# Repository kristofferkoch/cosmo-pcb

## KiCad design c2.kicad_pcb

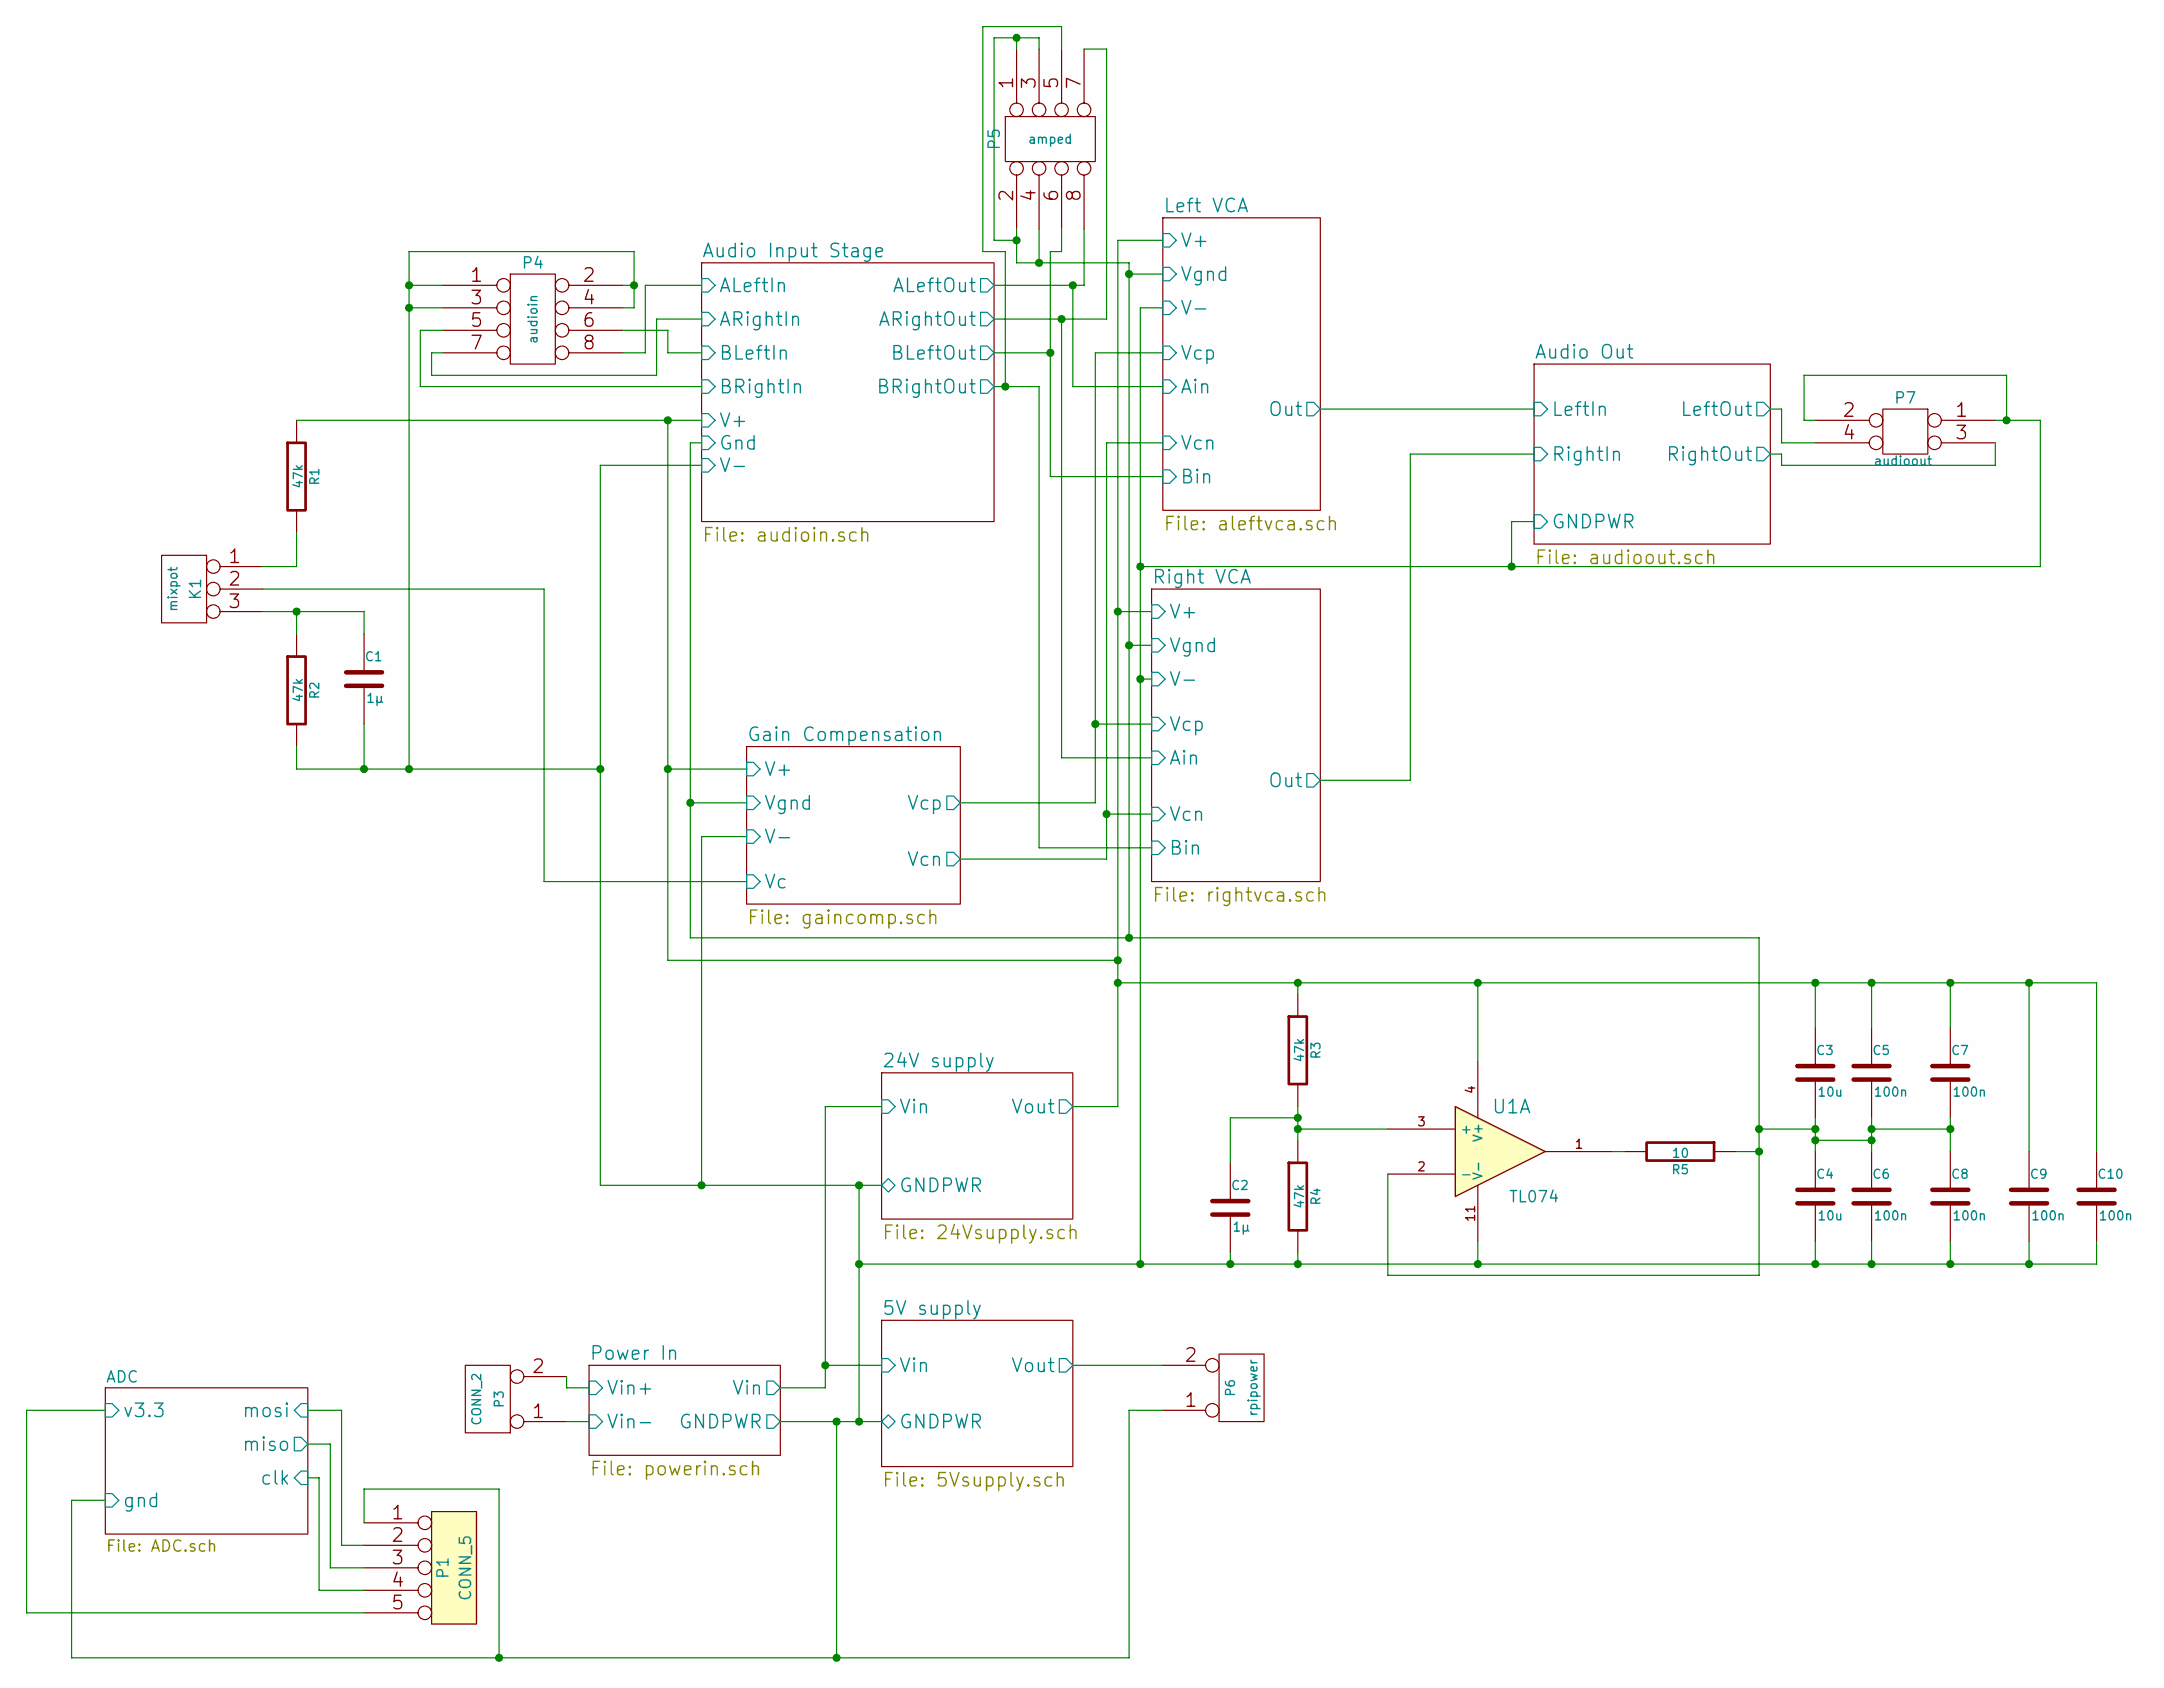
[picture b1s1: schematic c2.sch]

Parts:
C1, C2: 1µ
C3, C4: 10u
C5, C6, C7, C8, C9, C10: 100n
K1: mixpot
P1: CONN_5
P3: CONN_2
P4: audioin
P5: amped
P6: rpipower
P7: audioout
R1, R2, R3, R4: 47k
R5: 10
U1: TL074

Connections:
/5V supply/Vout: P6.2 (PM); also elsewhere on the board
/ADC/clk: P1.4; also elsewhere on the board
/ADC/miso: P1.3; also elsewhere on the board
/ADC/mosi: P1.2; also elsewhere on the board
/ADC/v3.3: P1.5; also elsewhere on the board
/Audio Input Stage/ALeftIn: P4.8; also elsewhere on the board
/Audio Input Stage/ALeftOut: P5.8; also elsewhere on the board
/Audio Input Stage/ARightIn: P4.7; also elsewhere on the board
/Audio Input Stage/ARightOut: P5.7; also elsewhere on the board
/Audio Input Stage/BLeftIn: P4.6; also elsewhere on the board
/Audio Input Stage/BLeftOut: P5.6; also elsewhere on the board
/Audio Input Stage/BRightIn: P4.5; also elsewhere on the board
/Audio Input Stage/BRightOut: P5.5; also elsewhere on the board
/Audio Input Stage/Gnd: C3.2, C4.1, C5.2, C6.1, C7.2, C8.1, P5.1, P5.2, P5.3, P5.4, R5.1, U1.2 (-); also elsewhere on the board
/Audio Input Stage/V+: C3.1, C5.1, C7.1, C9.1, C10.1, R1.1, R3.1, U1.4 (V+); also elsewhere on the board
/Audio Out/LeftOut: P7.4; also elsewhere on the board
/Audio Out/RightOut: P7.3; also elsewhere on the board
/Gain Compensation/Vc: K1.2 (PM); also elsewhere on the board
/Power In/Vin+: P3.2 (PM); also elsewhere on the board
GNDPWR: C1.2, C2.2, C4.2, C6.2, C8.2, C9.2, C10.2, P1.1, P3.1, P4.1, P4.2, P4.3, P4.4, P6.1, P7.1, P7.2, R2.2, R4.2, U1.11 (V-); also elsewhere on the board
unnamed: C1.1, K1.3, R2.1
unnamed: C2.1, R3.2, R4.1, U1.3 (+)
unnamed: K1.1, R1.2
unnamed: R5.2, U1.1

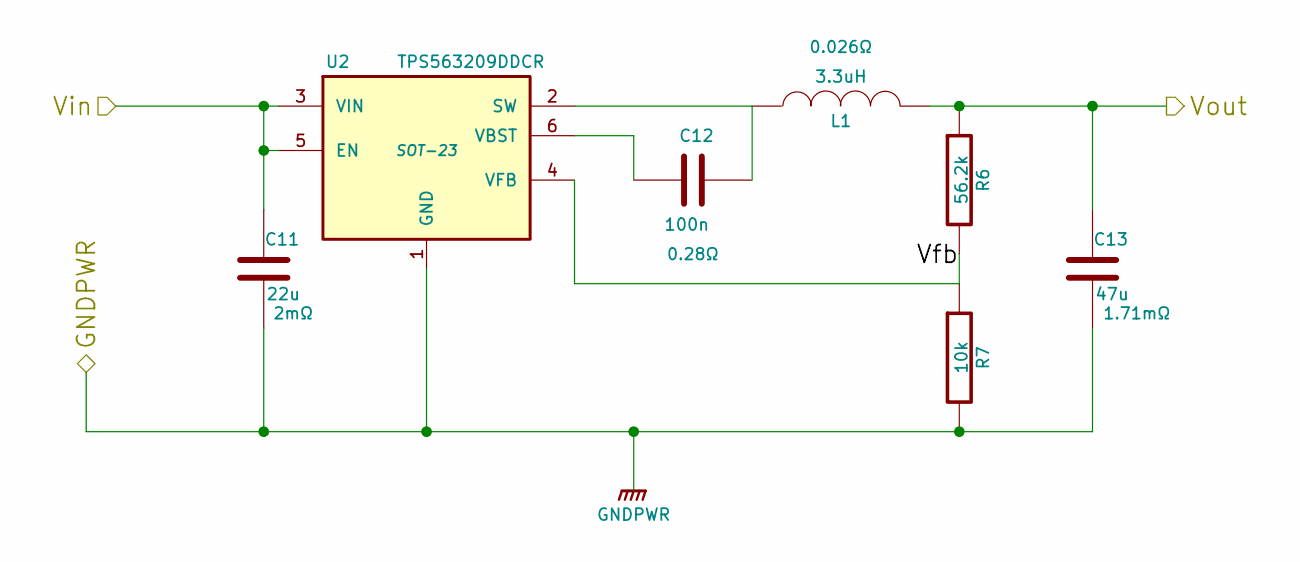
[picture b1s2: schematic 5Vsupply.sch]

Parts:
C11: 22u
C12: 100n
C13: 47u
L1: 3.3uH; Part XAL4030-332MEB
R6: 56.2k
R7: 10k
U2: TPS563209DDCR; SOT-23

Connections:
/5V supply/Vfb: R6.2, R7.1, U2.4 (VFB)
/5V supply/Vout: C13.1, L1.2, R6.1; also elsewhere on the board
/24V supply/Vin: C11.1, U2.3 (VIN), U2.5 (EN); also elsewhere on the board
GNDPWR: C11.2, C13.2, R7.2, U2.1 (GND); also elsewhere on the board
unnamed: C12.1, L1.1, U2.2 (SW)
unnamed: C12.2, U2.6 (VBST)

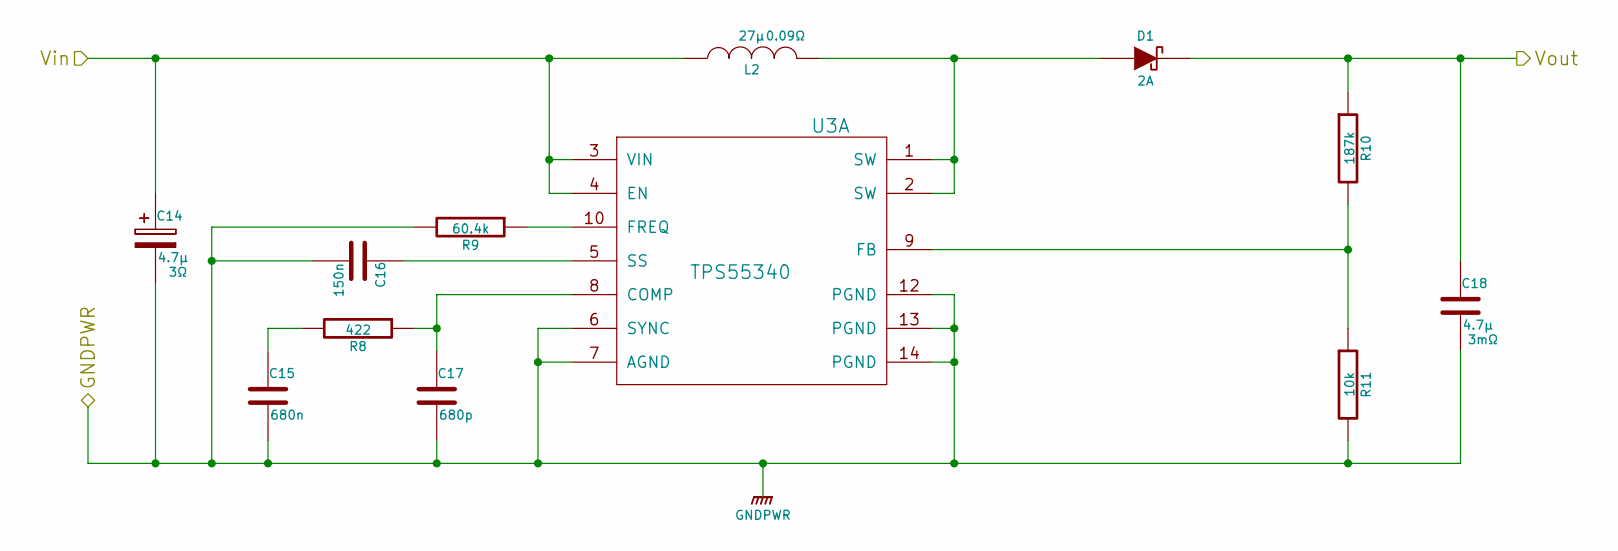
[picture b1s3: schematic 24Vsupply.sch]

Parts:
C14, C18: 4.7µ
C15: 680n
C16: 150n
C17: 680p
D1: 2A
L2: 27µ; Part DR0608-273L
R8: 422
R9: 60.4k
R10: 187k; Tolerance 1%
R11: 10k
U3: TPS55340

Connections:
/24V supply/Vin: C14.1, L2.1, U3.3 (VIN), U3.4 (EN); also elsewhere on the board
/Audio Input Stage/V+: C18.1, D1.2 (K), R10.1; also elsewhere on the board
GNDPWR: C14.2, C15.2, C16.2, C17.2, C18.2, R9.2, R11.2, U3.6 (SYNC), U3.7 (AGND), U3.12 (PGND), U3.13 (PGND), U3.14 (PGND); also elsewhere on the board
unnamed: C15.1, R8.2
unnamed: C16.1, U3.5 (SS)
unnamed: C17.1, R8.1, U3.8 (COMP)
unnamed: D1.1 (A), L2.2, U3.1 (SW), U3.2 (SW)
unnamed: R9.1, U3.10 (FREQ)
unnamed: R10.2, R11.1, U3.9 (FB)

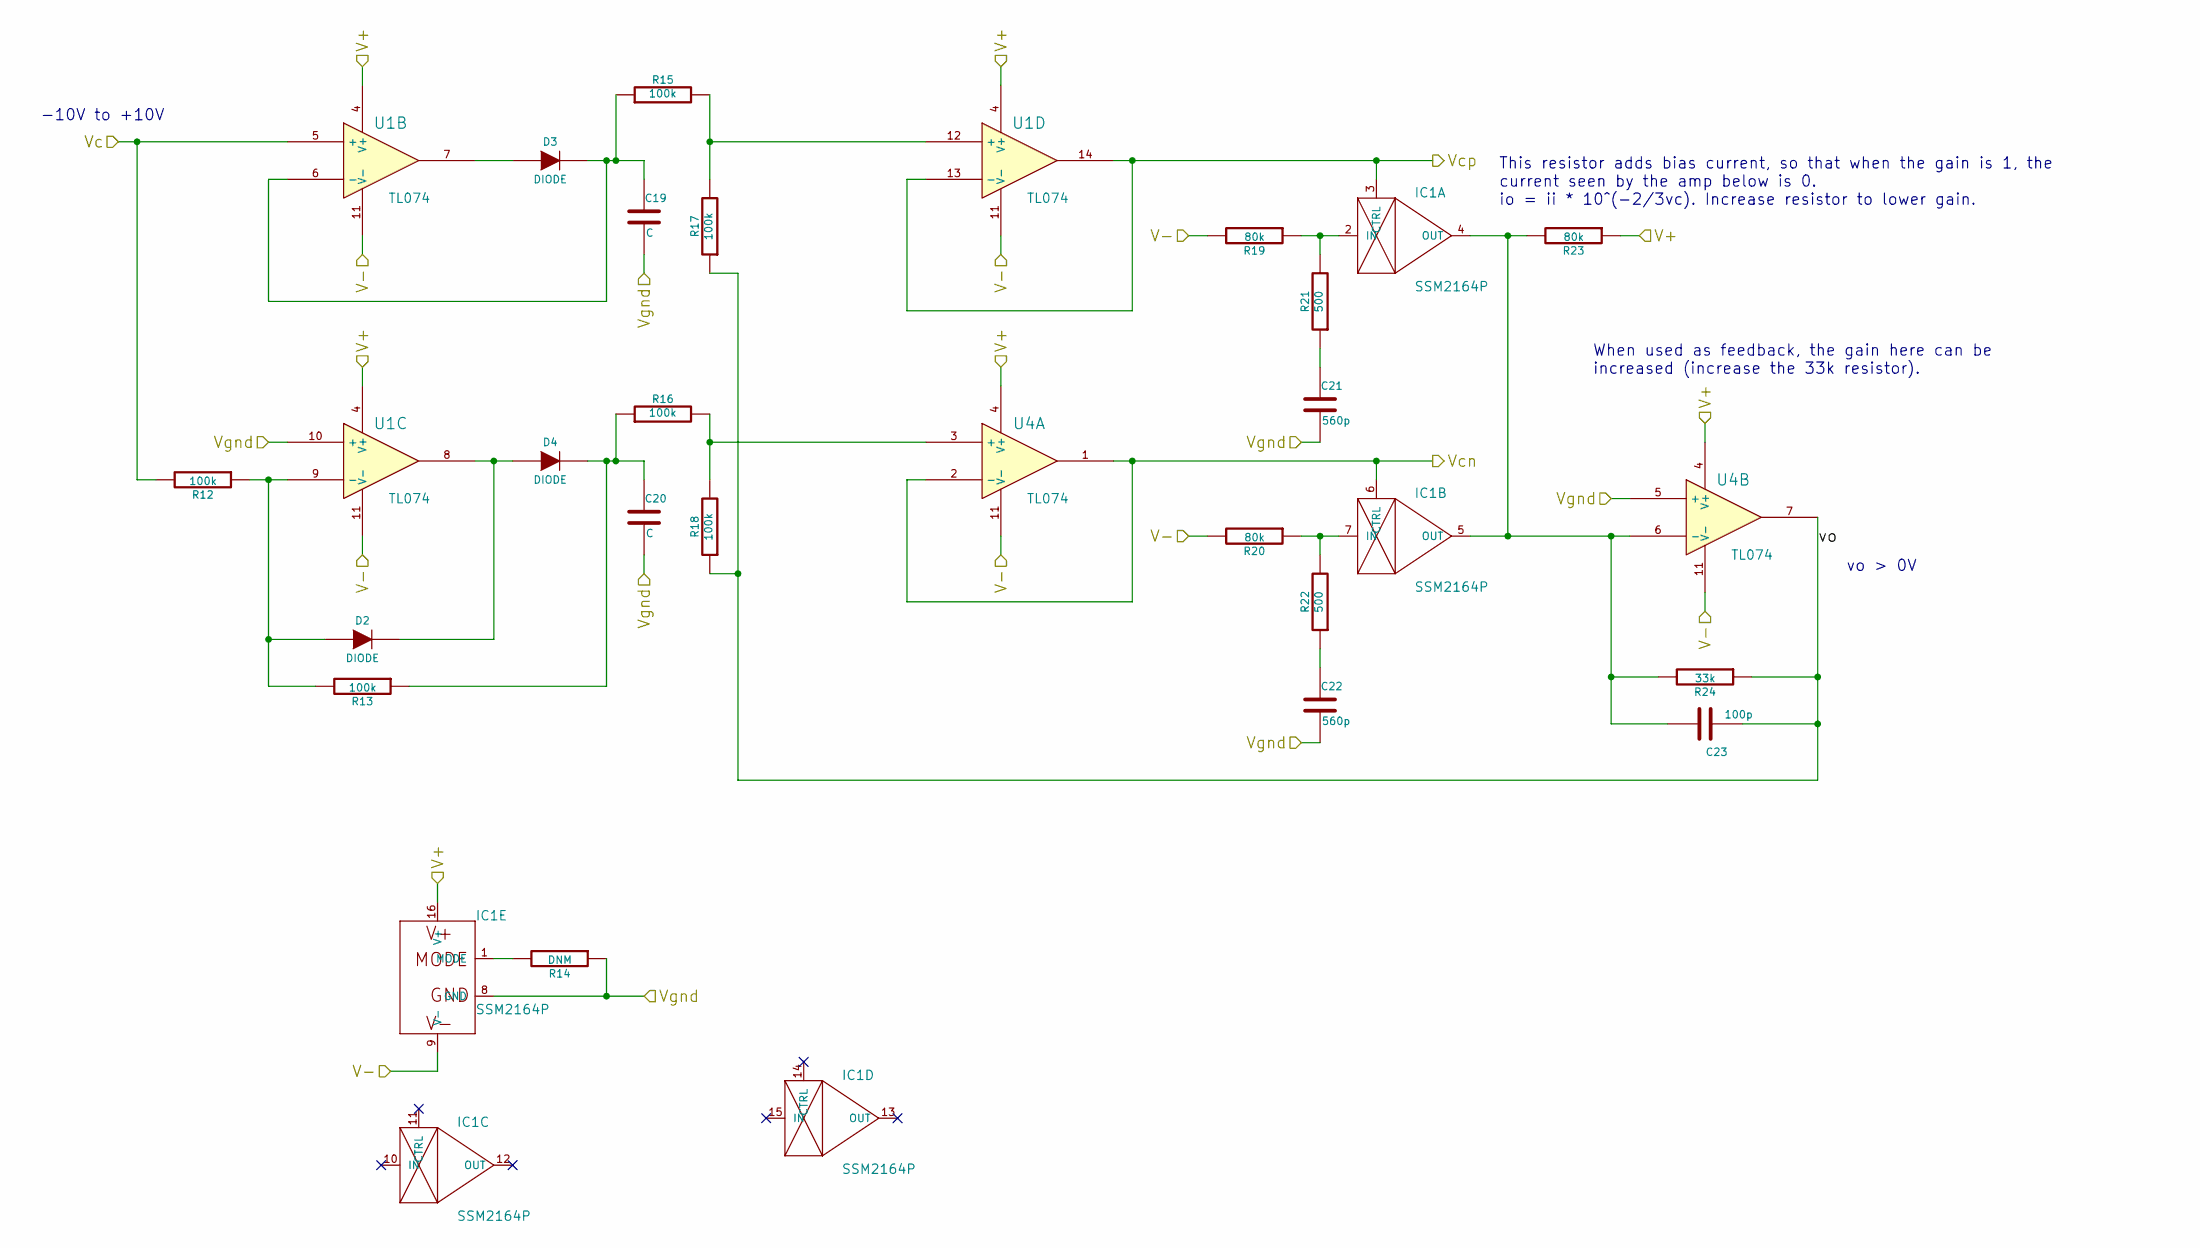
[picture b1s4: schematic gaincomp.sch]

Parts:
C19, C20: C
C21, C22: 560p
C23: 100p
D2, D3, D4: DIODE
IC1: SSM2164P; ssm2164-DIL16
R12, R13, R15, R16, R17, R18: 100k
R14: DNM
R19, R20, R23: 80k
R21, R22: 500
R24: 33k
U1, U4: TL074

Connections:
/Audio Input Stage/Gnd: C19.2, C20.2, C21.2, C22.2, IC1.8 (GND), R14.1, U1.10 (+), U4.5 (+); also elsewhere on the board
/Audio Input Stage/V+: IC1.16 (V+), R23.1, U1.4 (V+), U4.4 (V+); also elsewhere on the board
/Gain Compensation/Vc: R12.2, U1.5 (+); also elsewhere on the board
/Gain Compensation/Vcn: IC1.6 (CTRL), U4.1, U4.2 (-); also elsewhere on the board
/Gain Compensation/Vcp: IC1.3 (CTRL), U1.13 (-), U1.14; also elsewhere on the board
/Gain Compensation/vo: C23.1, R17.1, R18.1, R24.1, U4.7
GNDPWR: IC1.9 (V-), R19.2, R20.2, U1.11 (V-), U4.11 (V-); also elsewhere on the board
unnamed: C19.1, D3.2 (K), R15.1, U1.6 (-)
unnamed: C20.1, D4.2 (K), R13.1, R16.1
unnamed: C21.1, R21.1
unnamed: C22.1, R22.1
unnamed: C23.2, IC1.4 (OUT), IC1.5 (OUT), R23.2, R24.2, U4.6 (-)
unnamed: D2.1 (A), R12.1, R13.2, U1.9 (-)
unnamed: D2.2 (K), D4.1 (A), U1.8
unnamed: D3.1 (A), U1.7
unnamed: IC1.1 (MODE), R14.2
unnamed: IC1.2 (IN), R19.1, R21.2
unnamed: IC1.7 (IN), R20.1, R22.2
unnamed: R15.2, R17.2, U1.12 (+)
unnamed: R16.2, R18.2, U4.3 (+)

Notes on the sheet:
vo > 0V
When used as feedback, the gain here can be increased (increase the 33k resistor).
This resistor adds bias current, so that when the gain is 1, the current seen by the amp below is 0. io = ii * 10^(-2/3vc). Increase resistor to lower gain.
-10V to +10V

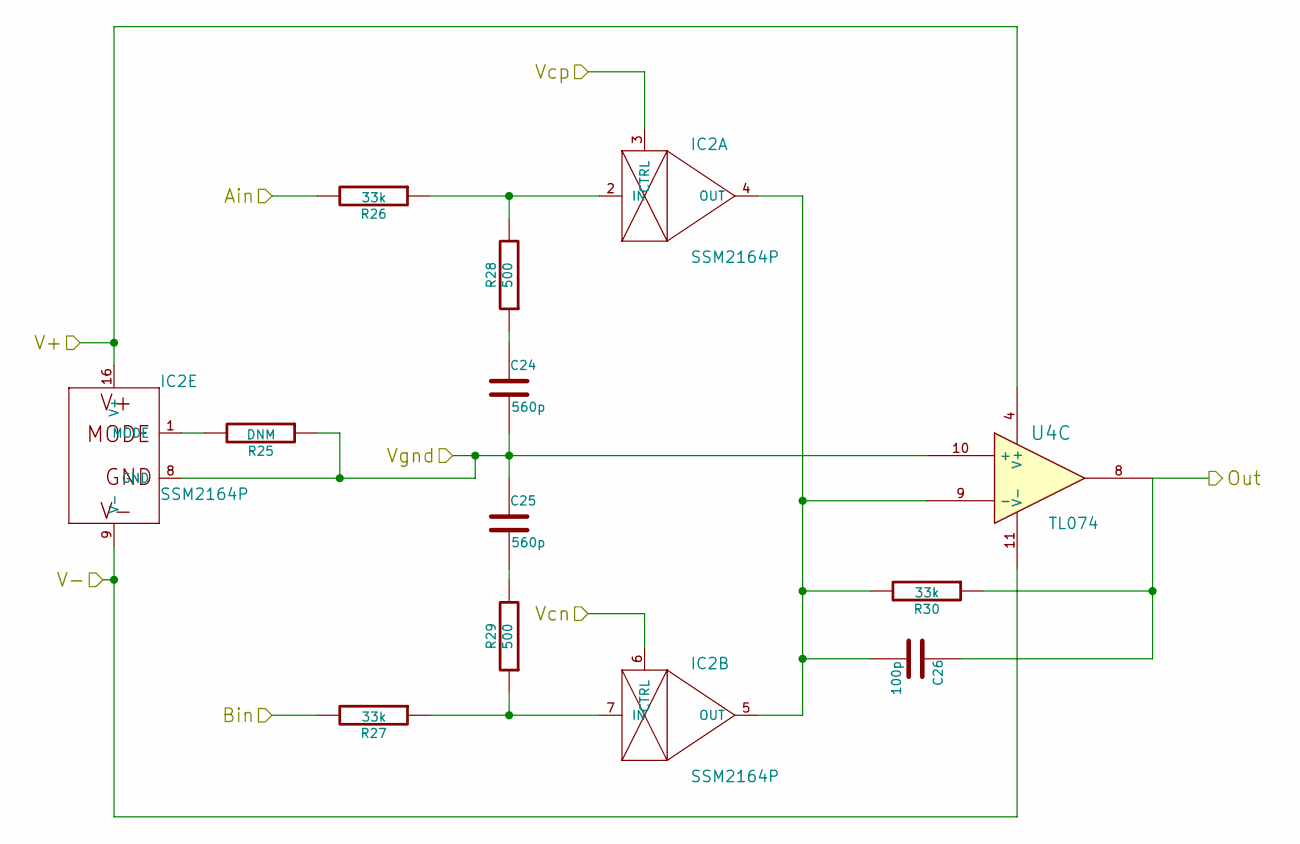
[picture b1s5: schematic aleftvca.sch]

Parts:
C24, C25: 560p
C26: 100p
IC2: SSM2164P; ssm2164-DIL16
R25: DNM
R26, R27, R30: 33k
R28, R29: 500
U4: TL074

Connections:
/Audio Input Stage/ALeftOut: R26.2; also elsewhere on the board
/Audio Input Stage/BLeftOut: R27.2; also elsewhere on the board
/Audio Input Stage/Gnd: C24.2, C25.1, IC2.8 (GND), R25.1, U4.10 (+); also elsewhere on the board
/Audio Input Stage/V+: IC2.16 (V+), U4.4 (V+); also elsewhere on the board
/Audio Out/LeftIn: C26.1, R30.1, U4.8; also elsewhere on the board
/Gain Compensation/Vcn: IC2.6 (CTRL); also elsewhere on the board
/Gain Compensation/Vcp: IC2.3 (CTRL); also elsewhere on the board
GNDPWR: IC2.9 (V-), U4.11 (V-); also elsewhere on the board
unnamed: C24.1, R28.1
unnamed: C25.2, R29.2
unnamed: C26.2, IC2.4 (OUT), IC2.5 (OUT), R30.2, U4.9 (-)
unnamed: IC2.1 (MODE), R25.2
unnamed: IC2.2 (IN), R26.1, R28.2
unnamed: IC2.7 (IN), R27.1, R29.1

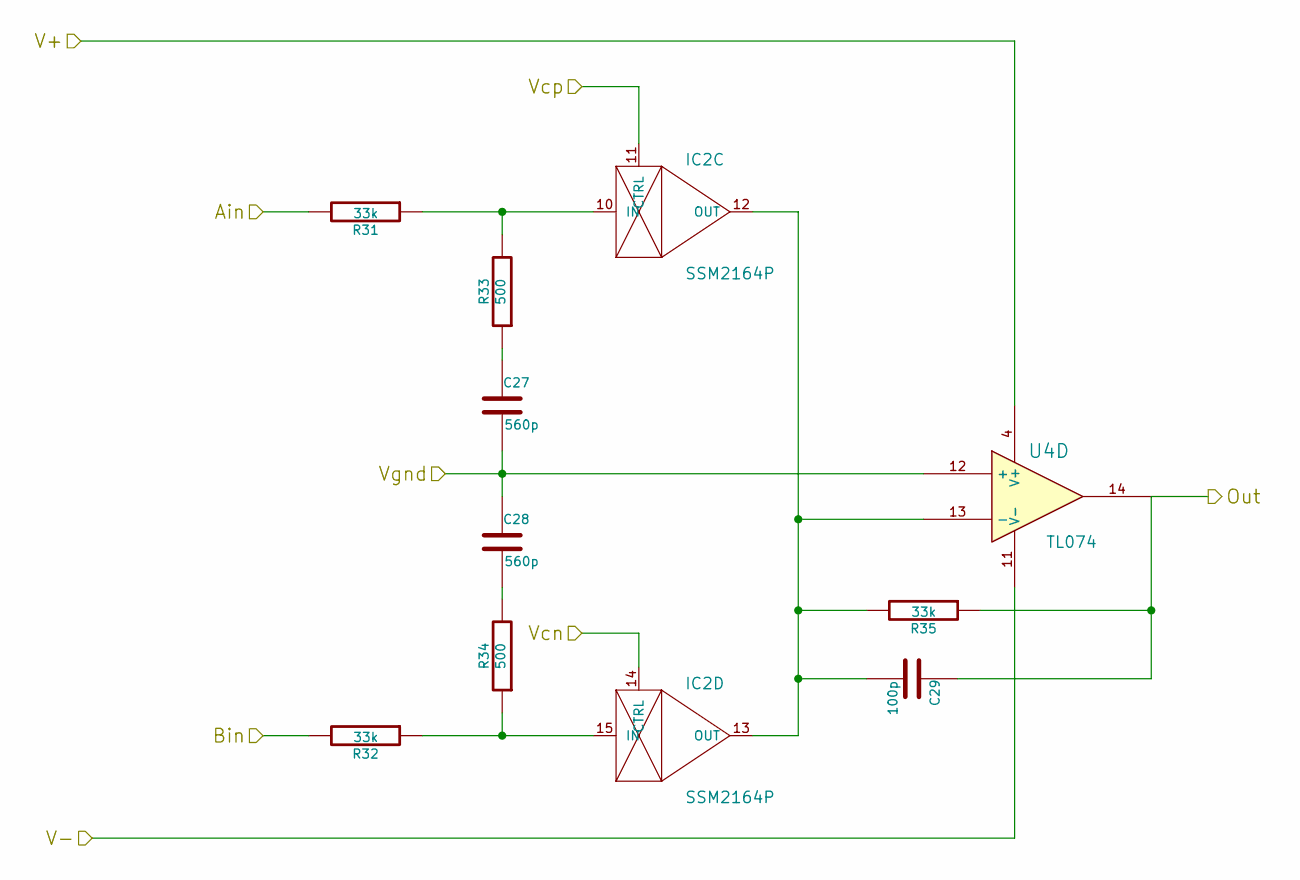
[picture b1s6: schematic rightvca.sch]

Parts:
C27, C28: 560p
C29: 100p
IC2: SSM2164P; ssm2164-DIL16
R31, R32, R35: 33k
R33, R34: 500
U4: TL074

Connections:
/Audio Input Stage/ARightOut: R31.2; also elsewhere on the board
/Audio Input Stage/BRightOut: R32.2; also elsewhere on the board
/Audio Input Stage/Gnd: C27.2, C28.1, U4.12 (+); also elsewhere on the board
/Audio Input Stage/V+: U4.4 (V+); also elsewhere on the board
/Gain Compensation/Vcn: IC2.14 (CTRL); also elsewhere on the board
/Gain Compensation/Vcp: IC2.11 (CTRL); also elsewhere on the board
/Right VCA/Out: C29.1, R35.1, U4.14; also elsewhere on the board
GNDPWR: U4.11 (V-); also elsewhere on the board
unnamed: C27.1, R33.1
unnamed: C28.2, R34.2
unnamed: C29.2, IC2.12 (OUT), IC2.13 (OUT), R35.2, U4.13 (-)
unnamed: IC2.10 (IN), R31.1, R33.2
unnamed: IC2.15 (IN), R32.1, R34.1

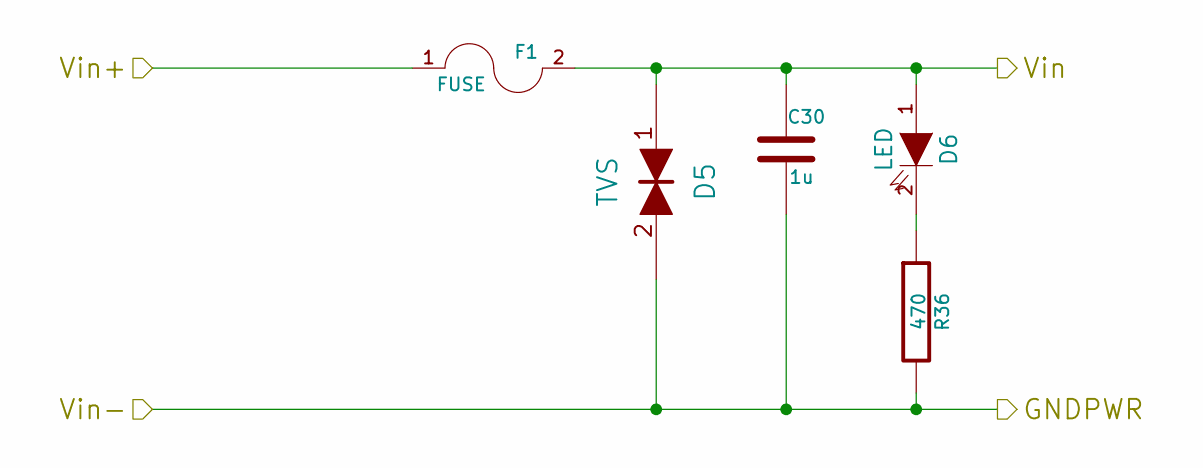
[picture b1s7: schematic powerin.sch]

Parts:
C30: 1u
D5: TVS
D6: LED
F1: FUSE
R36: 470

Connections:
/24V supply/Vin: C30.1, D5.1, D6.1 (A), F1.2; also elsewhere on the board
/Power In/Vin+: F1.1; also elsewhere on the board
GNDPWR: C30.2, D5.2, R36.2; also elsewhere on the board
unnamed: D6.2 (K), R36.1

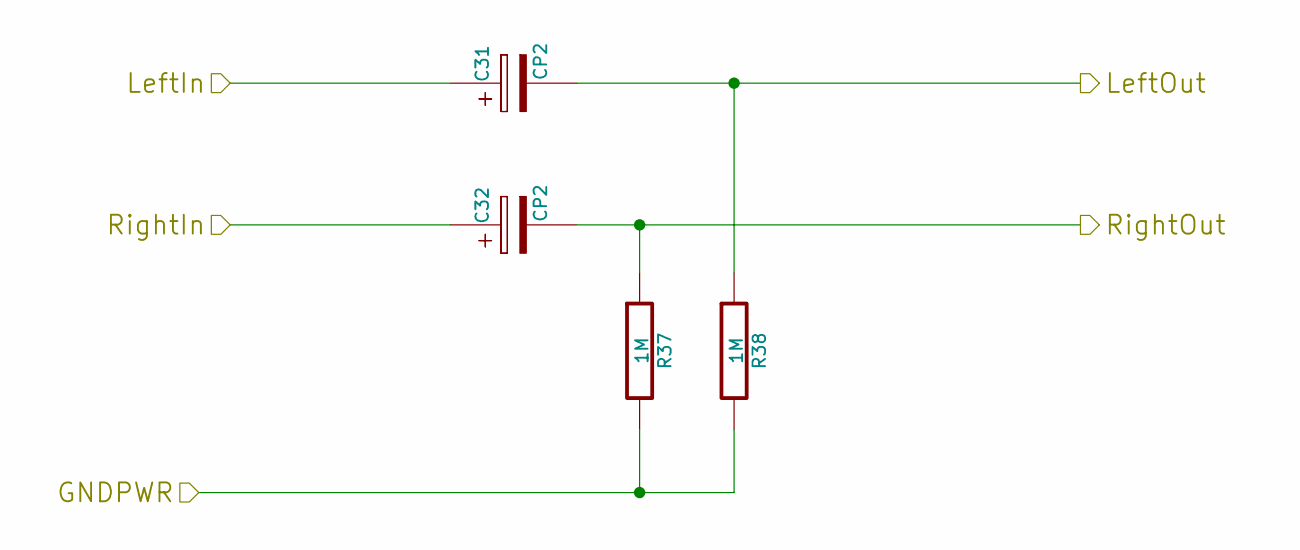
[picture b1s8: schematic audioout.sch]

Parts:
C31, C32: CP2
R37, R38: 1M

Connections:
/Audio Out/LeftIn: C31.1; also elsewhere on the board
/Audio Out/LeftOut: C31.2, R38.1; also elsewhere on the board
/Audio Out/RightOut: C32.2, R37.1; also elsewhere on the board
/Right VCA/Out: C32.1; also elsewhere on the board
GNDPWR: R37.2, R38.2; also elsewhere on the board

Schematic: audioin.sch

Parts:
C33, C34, C37, C38: 22p
C35, C36, C39, C40: 100n
R39, R40, R45, R46: 1M
R41, R42, R43, R44, R47, R48, R49, R50: 100k
U5: TL074

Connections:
/Audio Input Stage/ALeftIn: C33.1, C35.2; also elsewhere on the board
/Audio Input Stage/ALeftOut: R43.1, U5.1; also elsewhere on the board
/Audio Input Stage/ARightIn: C34.1, C36.2; also elsewhere on the board
/Audio Input Stage/ARightOut: R44.1, U5.7; also elsewhere on the board
/Audio Input Stage/BLeftIn: C37.1, C39.2; also elsewhere on the board
/Audio Input Stage/BLeftOut: R49.1, U5.8; also elsewhere on the board
/Audio Input Stage/BRightIn: C38.1, C40.2; also elsewhere on the board
/Audio Input Stage/BRightOut: R50.1, U5.14; also elsewhere on the board
/Audio Input Stage/Gnd: R39.2, R40.2, R41.2, R42.2, R45.2, R46.2, R47.2, R48.2; also elsewhere on the board
/Audio Input Stage/V+: U5.4 (V+); also elsewhere on the board
GNDPWR: C33.2, C34.2, C37.2, C38.2, U5.11 (V-); also elsewhere on the board
unnamed: C35.1, R39.1, U5.3 (+)
unnamed: C36.1, R40.1, U5.5 (+)
unnamed: C39.1, R45.1, U5.10 (+)
unnamed: C40.1, R46.1, U5.12 (+)
unnamed: R41.1, R43.2, U5.2 (-)
unnamed: R42.1, R44.2, U5.6 (-)
unnamed: R47.1, R49.2, U5.9 (-)
unnamed: R48.1, R50.2, U5.13 (-)

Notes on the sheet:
TVS dioder!

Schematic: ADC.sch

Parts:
C41, C42, C43, C44, C45: 100n
K2: AD0
K3: AD1
K4: AD2
K5: AD3
R51, R52, R53, R54: 10k
U6: MCP3008

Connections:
/ADC/clk: U6.13 (CLK); also elsewhere on the board
/ADC/miso: U6.12 (DOUT); also elsewhere on the board
/ADC/mosi: U6.11 (DIN); also elsewhere on the board
/ADC/v3.3: U6.16 (VDD); also elsewhere on the board
GNDPWR: C41.2, C42.2, C43.2, C44.2, C45.2, K2.3, K3.3, K4.3, K5.3, U6.5 (CH4), U6.6 (CH5), U6.7 (CH6), U6.8 (CH7), U6.9 (DGND), U6.10 (~CS~/SHDN), U6.14 (AGND); also elsewhere on the board
unnamed: C41.1, K2.1, K3.1, K4.1, K5.1, U6.15 (VREF)
unnamed: C42.1, R51.2, U6.1 (CH0)
unnamed: C43.1, R52.2, U6.2 (CH1)
unnamed: C44.1, R53.2, U6.3 (CH2)
unnamed: C45.1, R54.2, U6.4 (CH3)
unnamed: K2.2 (PM), R51.1
unnamed: K3.2 (PM), R52.1
unnamed: K4.2 (PM), R53.1
unnamed: K5.2 (PM), R54.1

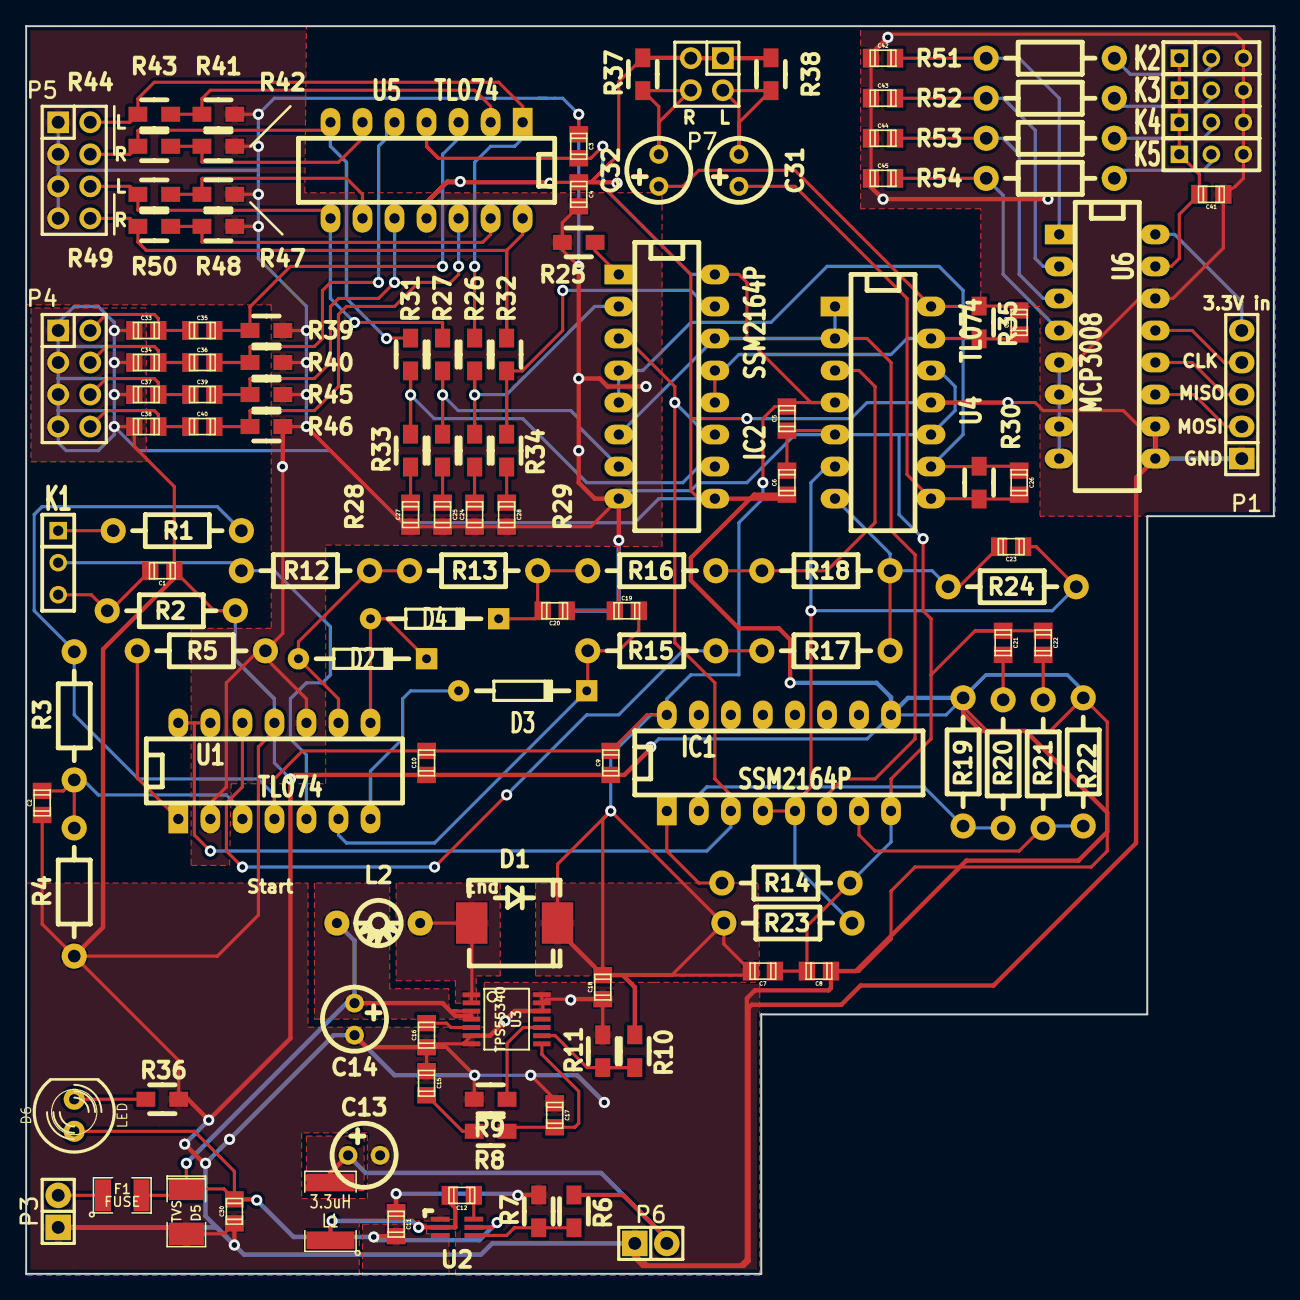
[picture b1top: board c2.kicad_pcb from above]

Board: 2 copper layers, 98.9 x 98.9 mm, 127 parts (0 on the bottom side), 81 nets.

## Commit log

2014-11-11 Added top-level connections
2015-01-01 Unknown changes
2015-03-10 Some work
2015-03-22 Ready for tapeout
2015-03-30 Tapeout
